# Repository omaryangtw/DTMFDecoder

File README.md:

# DTMFDecoder

A DTMF Decoder development kit designed with KiCad

This is an implementation of SM8223 Application Circuit and integrated with ESP32 Devkit. Makes it handy to retrieve CID(Caller Identification) and handle through both serial port and HTTP requests.

## Components

- ESP32-WROOM-32D DevKit
- [SM8223](https://pdf.dzsc.com/88889/22272.pdf) IC

## IO

### ESP32

IO25 : Read DTMF Signals at the baud rate of 1200
IO33 : indicates the signal type (FSK/DTMF)

## PCB / SMT

GBR is included so that it can go through PCB / SMT process directly

## LICENSE

MIT

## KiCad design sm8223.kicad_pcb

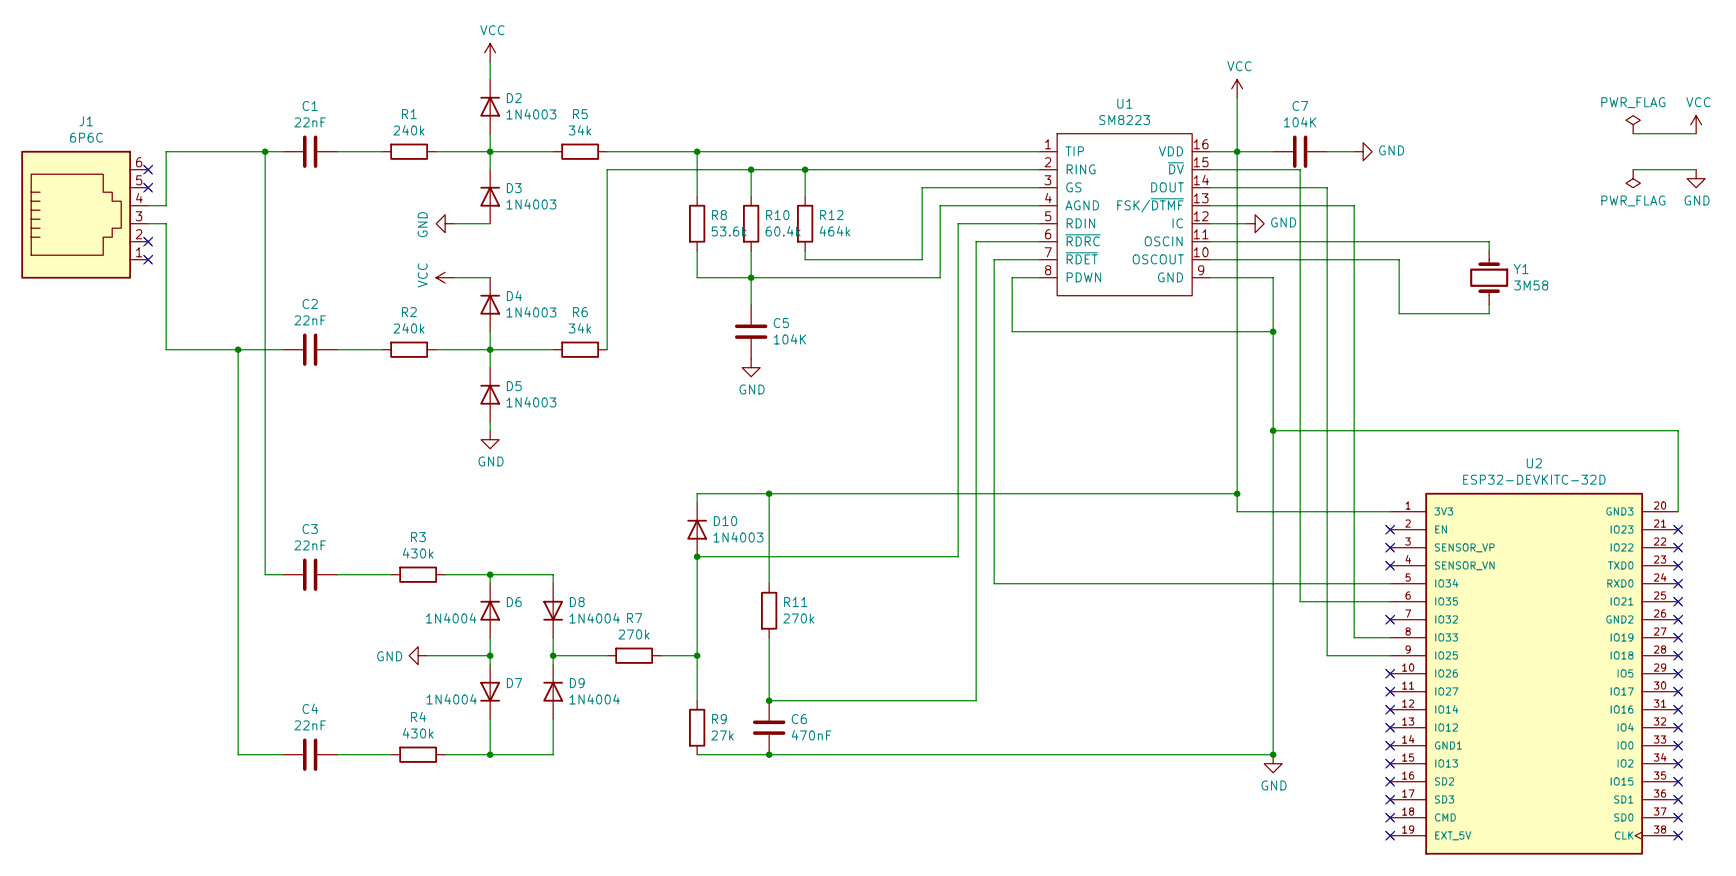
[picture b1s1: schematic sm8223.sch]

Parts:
C1, C2, C3, C4: 22nF; C_0603_1608Metric
C5, C7: 104K; C_0603_1608Metric
C6: 470nF; C_0603_1608Metric
D2, D3, D4, D5, D10: 1N4003; D_DO-41_SOD81_P7.62mm_Horizontal
D6, D7, D8, D9: 1N4004; D_DO-41_SOD81_P7.62mm_Horizontal
J1: 6P6C; RJ12_Amphenol_54601
R1, R2: 240k; C_0603_1608Metric
R3, R4: 430k; C_0603_1608Metric
R5, R6: 34k; C_0603_1608Metric
R7, R11: 270k; C_0603_1608Metric
R8: 53.6k; C_0603_1608Metric
R9: 27k; C_0603_1608Metric
R10: 60.4k; C_0603_1608Metric
R12: 464k; C_0603_1608Metric
U1: SM8223; DIP-16_W7.62mm
U2: ESP32-DEVKITC-32D; MODULE_ESP32-DEVKITC-32D; PARTREV 4
Y1: 3M58; Crystal_HC49-4H_Vertical

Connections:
GND: C5.2, C6.2, C7.1, D3.2 (A), D5.2 (A), D6.2 (A), D7.2 (A), R9.2, U1.8 (PDWN), U1.9 (GND), U1.12 (IC), U2.20 (GND3)
unnamed: C1.1, R1.2
unnamed: C1.2, C3.2, J1.4
unnamed: C2.1, R2.2
unnamed: C2.2, C4.2, J1.3
unnamed: C3.1, R3.2
unnamed: C4.1, R4.2
unnamed: C5.1, R8.2, R10.2, U1.4 (AGND)
unnamed: C6.1, R11.2, U1.6 (~RDRC)
unnamed: D2.2 (A), D3.1 (K), R1.1, R5.2
unnamed: D4.2 (A), D5.1 (K), R2.1, R6.2
unnamed: D6.1 (K), D8.2 (A), R3.1
unnamed: D7.1 (K), D9.2 (A), R4.1
unnamed: D8.1 (K), D9.1 (K), R7.2
unnamed: D10.2 (A), R7.1, R9.1, U1.5 (RDIN)
unnamed: R5.1, R8.1, U1.1 (TIP)
unnamed: R6.1, R10.1, R12.1, U1.2 (RING)
unnamed: R12.2, U1.3 (GS)
unnamed: U1.7 (~RDET), U2.5 (IO34)
unnamed: U1.10 (OSCOUT), Y1.2
unnamed: U1.11 (OSCIN), Y1.1
unnamed: U1.13 (FSK/~DTMF), U2.8 (IO33)
unnamed: U1.14 (DOUT), U2.9 (IO25)
unnamed: U1.15 (~DV), U2.6 (IO35)
VCC: C7.2, D2.1 (K), D4.1 (K), D10.1 (K), R11.1, U1.16 (VDD), U2.1 (3V3)

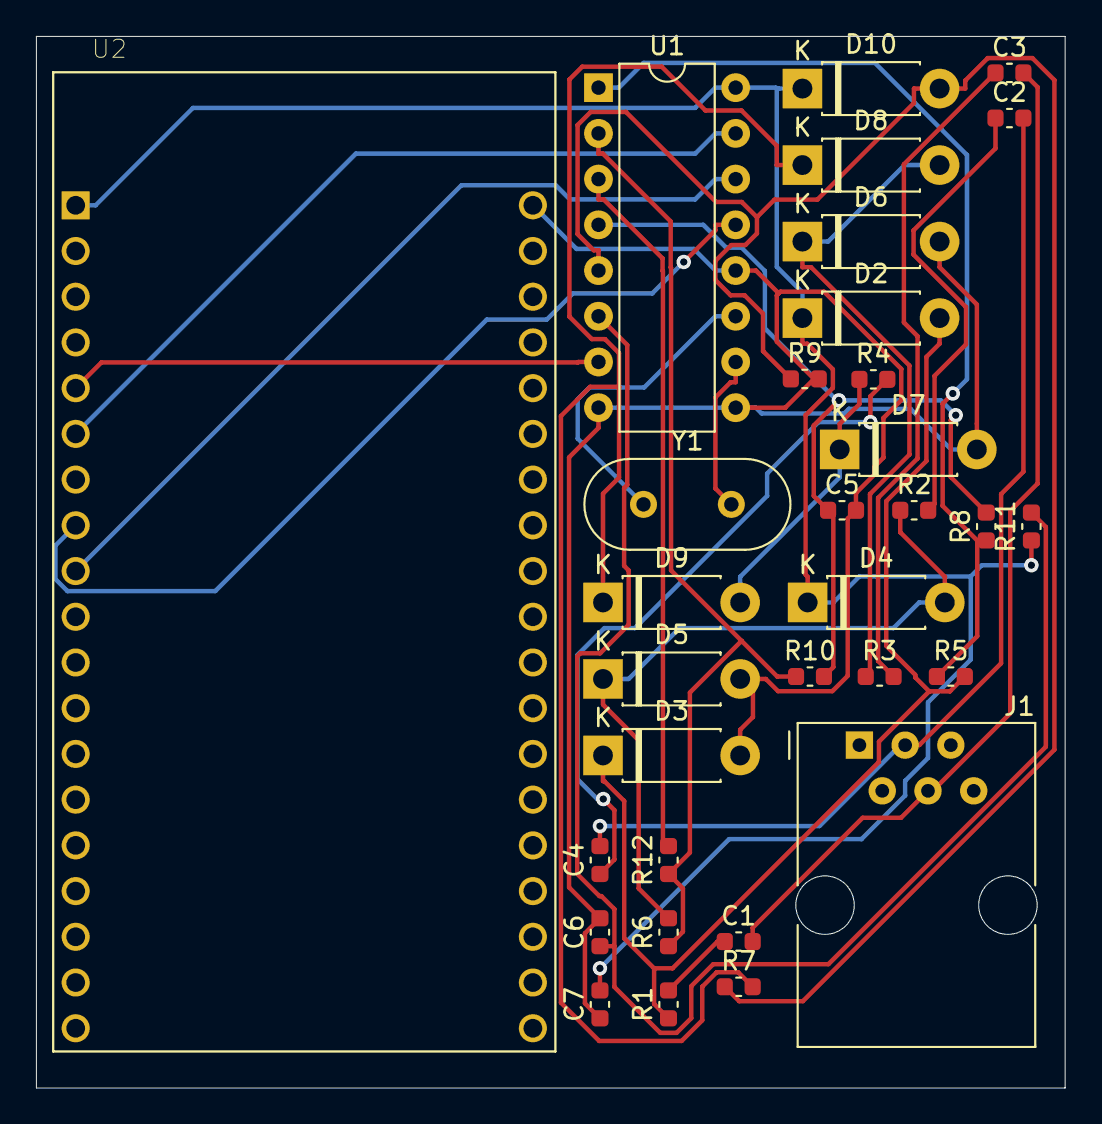
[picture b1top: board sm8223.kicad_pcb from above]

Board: 2 copper layers, 57.1 x 58.4 mm, 32 parts (0 on the bottom side), 25 nets.

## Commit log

2022-01-06 documentation
